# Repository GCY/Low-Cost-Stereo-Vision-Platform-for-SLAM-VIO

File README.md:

# Low-Cost-Stereo-Vision-Platform-for-SLAM-VIO

 - Step 1. Capture the [chessboard pattern](https://raw.githubusercontent.com/opencv/opencv/master/doc/pattern.png) picture from Left and Right Camera.
 - Step 2. Run "Stereo Camera Calibration"
 - Step 3. Calibration stereo camera phase, execute initUndistortRectifyMap with "extrinsics.yml" and "intrinsics.yml" befor cv::remap
 - Step 4. Create StereoBM or SGBM object to calculate depth map.
 - Step 5. Cet point cloud from depth map and baseline.

## Mac OS X

### Dependence
 - wxWidgets 3.0.4
 - OpenCV 4.4.0
 - libcurl 7.54.0
 
### Build

```cpp

cd ./App/Mac/wxStereoCamera
make

```

## Win10

### Dependence
 - wxWidgets 3.1.4
 - OpenCV 4.4.0
 - libcurl 7.67.0
 
 ### Build
 ```cpp
 Build App/Win10/wxStereoCamera/wxStereoCamera.sln with Visual Studio Community 2019
 ```

## Reference
 - [ESP32 CAM MJPEG Stream Decoder and Control Library](https://github.com/GCY/ESP32-CAM-MJPEG-Stream-Decoder-and-Control-Library)

Licensing
=======
Copyright (C) 2020  TonyGUO <https://github.com/GCY>.

This program is free software: you can redistribute it and/or modify
it under the terms of the GNU General Public License as published by
the Free Software Foundation, either version 3 of the License, or
(at your option) any later version.

This program is distributed in the hope that it will be useful,
but WITHOUT ANY WARRANTY; without even the implied warranty of
MERCHANTABILITY or FITNESS FOR A PARTICULAR PURPOSE.  See the
GNU General Public License for more details.

You should have received a copy of the GNU General Public License
along with this program.  If not, see <http://www.gnu.org/licenses/>.

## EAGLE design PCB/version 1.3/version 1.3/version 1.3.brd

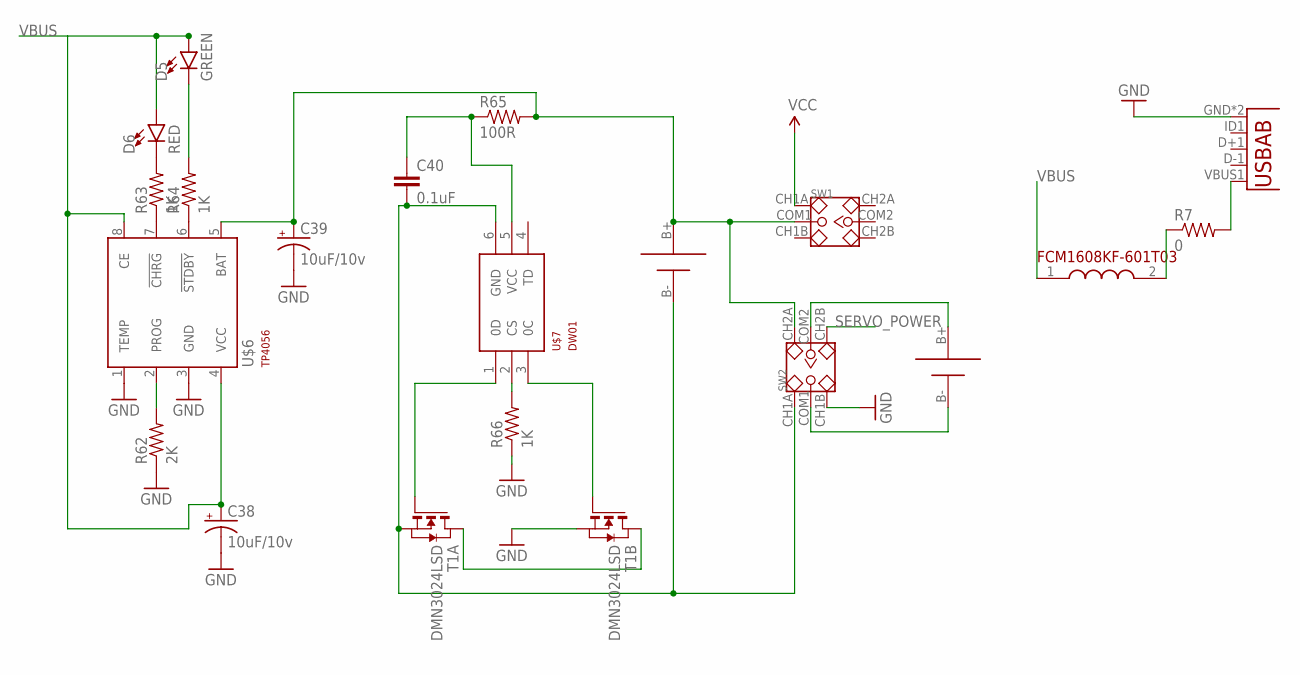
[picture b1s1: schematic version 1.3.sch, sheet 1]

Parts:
C38, C39: 10uF/10v; EIA3216-KIT
C40: 0.1uF; 0603-CAP
D5: GREEN; LED-0603
D6: RED; LED-0603
R7: 0; 0805
R62: 2K; 0603-RES
R63, R64, R66: 1K; 0603-RES
R65: 100R; 0603-RES
SW1, SW2: SMD-TOGGLE-SWITCH-2CH(2X3P-7X3.5MM); SW6-2.54-SMD-7.0X3.5X1.5MM
T1: DMN3024LSD; TSSOP-8
U1: USB""; USB-MICRO-SMD
U$4: FCM1608KF-601T03
U$5, U$8: 18650SMD
U$6: TP4056; SOT23-8
U$7: DW01; SOT23-6

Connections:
GND: C38.C (-), C39.C (-), R62.1, R66.1, SW2.CH1B, T1.6 (S), T1.7 (S), U1.GND, U1.GND1 (GND), U$6.1 (TEMP), U$6.3 (GND); also elsewhere on the board
unnamed: R7.2, U1.VBUS1 (VBUS)
unnamed: C39.A (+), R65.2, SW1.COM1, SW2.CH2A, U$5.B+, U$6.5 (BAT)
unnamed: SW2.COM2, U$8.B+
unnamed: SW2.COM1, U$8.B-
unnamed: R7.1, U$4.2 (2.OUT)
unnamed: R62.2, U$6.2 (PROG)
unnamed: R63.1, U$6.7 (!CHRG)
unnamed: R64.1, U$6.6 (!STDBY)
unnamed: D6.C, R63.2
unnamed: D5.C, R64.2
unnamed: C40.1, R65.1, U$7.5 (VCC)
unnamed: C40.2, SW2.CH1A, T1.2 (S), T1.3 (S), U$5.B-, U$7.6 (GND)
unnamed: T1.4 (G), U$7.1 (0D)
unnamed: R66.2, U$7.2 (CS)
unnamed: T1.1 (D), T1.8 (D)
unnamed: T1.5 (G), U$7.3 (0C)
SERVO_POWER: SW2.CH2B; also elsewhere on the board
VBUS: C38.A (+), D5.A, D6.A, U$4.1 (1.IN), U$6.4 (VCC), U$6.8 (CE)
VCC: SW1.CH1A; also elsewhere on the board

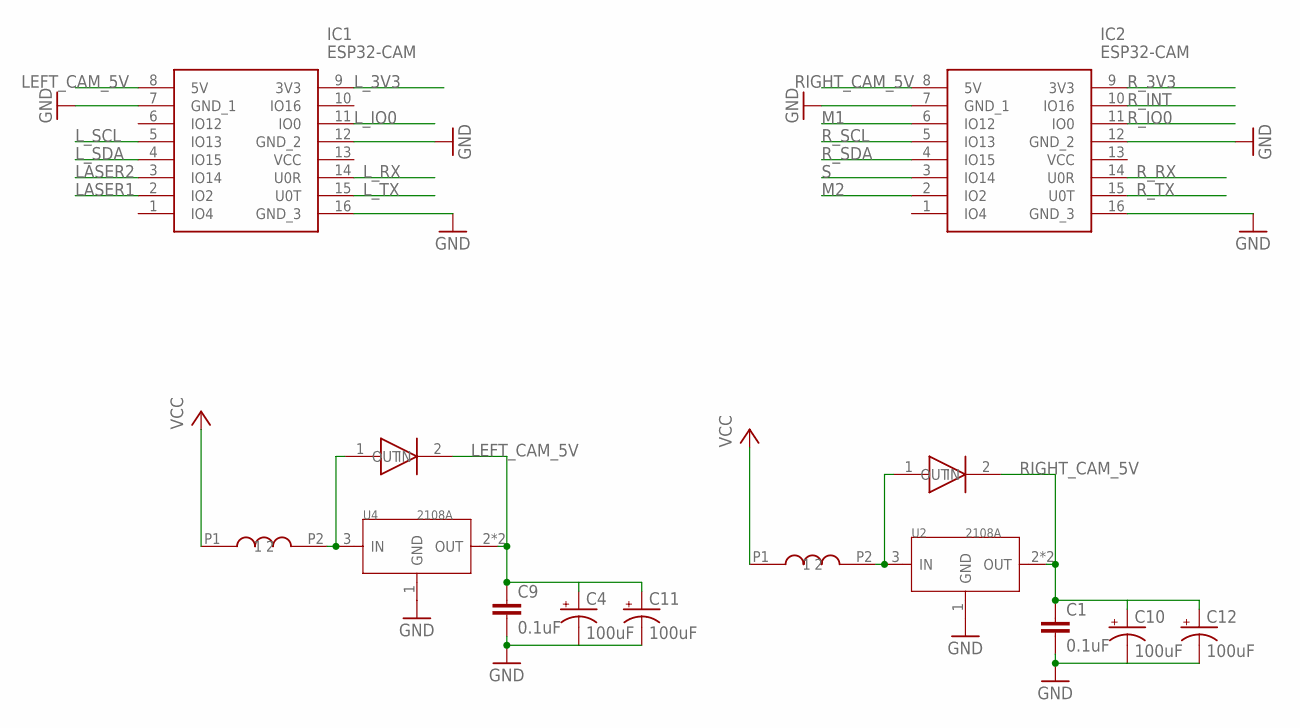
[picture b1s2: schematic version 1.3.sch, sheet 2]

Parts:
C1, C9: 0.1uF; 0603-CAP
C4, C10, C11, C12: 100uF; E/7260-38R
IC1, IC2: ESP32-CAM; ESP32CAM
U2, U4: 2108A; SOT-89
U$13, U$16: CD54
U$14, U$15: SMA-SS34

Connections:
GND: C1.2, C4.-, C9.2, C10.-, C11.-, C12.-, IC1.7 (GND_1), IC1.12 (GND_2), IC1.16 (GND_3), IC2.7 (GND_1), IC2.12 (GND_2), IC2.16 (GND_3), U2.1 (GND), U4.1 (GND); also elsewhere on the board
LASER1: IC1.2 (IO2); also elsewhere on the board
LASER2: IC1.3 (IO14); also elsewhere on the board
LEFT_CAM_5V: C4.+, C9.1, C11.+, IC1.8 (5V), U4.2 (OUT), U4.4 (OUT), U$14.2 (OUT); also elsewhere on the board
L_3V3: IC1.9 (3V3); also elsewhere on the board
L_IO0: IC1.11 (IO0); also elsewhere on the board
L_RX: IC1.14 (U0R); also elsewhere on the board
L_SCL: IC1.5 (IO13); also elsewhere on the board
L_SDA: IC1.4 (IO15); also elsewhere on the board
L_TX: IC1.15 (U0T); also elsewhere on the board
M1: IC2.6 (IO12); also elsewhere on the board
M2: IC2.2 (IO2); also elsewhere on the board
unnamed: U4.3 (IN), U$13.P2 (2), U$14.1 (IN)
unnamed: U2.3 (IN), U$15.1 (IN), U$16.P2 (2)
RIGHT_CAM_5V: C1.1, C10.+, C12.+, IC2.8 (5V), U2.2 (OUT), U2.4 (OUT), U$15.2 (OUT); also elsewhere on the board
R_3V3: IC2.9 (3V3); also elsewhere on the board
R_INT: IC2.10 (IO16); also elsewhere on the board
R_IO0: IC2.11 (IO0); also elsewhere on the board
R_RX: IC2.14 (U0R); also elsewhere on the board
R_SCL: IC2.5 (IO13); also elsewhere on the board
R_SDA: IC2.4 (IO15); also elsewhere on the board
R_TX: IC2.15 (U0T); also elsewhere on the board
S: IC2.3 (IO14); also elsewhere on the board
VCC: U$13.P1 (1), U$16.P1 (1); also elsewhere on the board

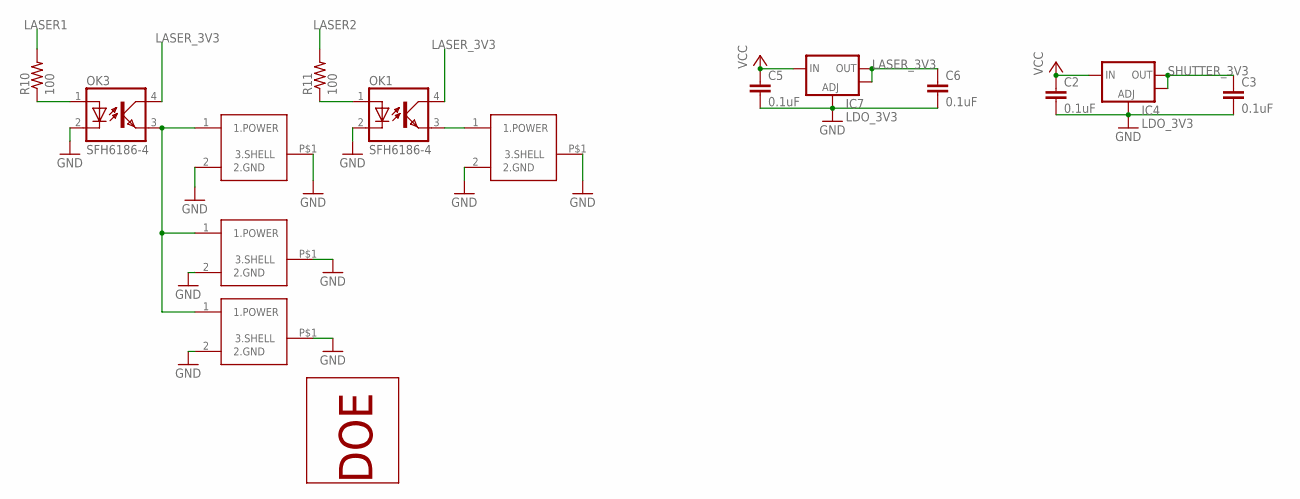
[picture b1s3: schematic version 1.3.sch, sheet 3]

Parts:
C2, C3, C5, C6: 0.1uF; 0603-CAP
IC4, IC7: LDO_3V3; SOT223
OK1, OK3: SFH6186-4; SMD4-7
R10, R11: 100; 0603-RES
U$1, U$2, U$9: OD-6.5MM-LASER
U$3: DOE-MODULE
U$20: OD-12MM-LASER

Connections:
GND: C2.2, C3.2, C5.2, C6.2, IC4.1 (ADJ), IC7.1 (ADJ), OK1.2 (C), OK3.2 (C), U$1.2 (2.GND), U$1.P$1 (3.SHELL), U$2.2 (2.GND), U$2.P$1 (3.SHELL), U$9.2 (2.GND), U$9.P$1 (3.SHELL), U$20.2 (2.GND), U$20.P$1 (3.SHELL); also elsewhere on the board
LASER1: R10.2; also elsewhere on the board
LASER2: R11.2; also elsewhere on the board
LASER_3V3: C6.1, IC7.2 (OUT), IC7.4 (OUT), OK1.4 (COL), OK3.4 (COL)
unnamed: OK3.3 (EMIT), U$1.1 (1.POWER), U$2.1 (1.POWER), U$9.1 (1.POWER)
unnamed: OK1.3 (EMIT), U$20.1 (1.POWER)
unnamed: OK3.1 (A), R10.1
unnamed: OK1.1 (A), R11.1
SHUTTER_3V3: C3.1, IC4.2 (OUT), IC4.4 (OUT); also elsewhere on the board
VCC: C2.1, C5.1, IC4.3 (IN), IC7.3 (IN); also elsewhere on the board

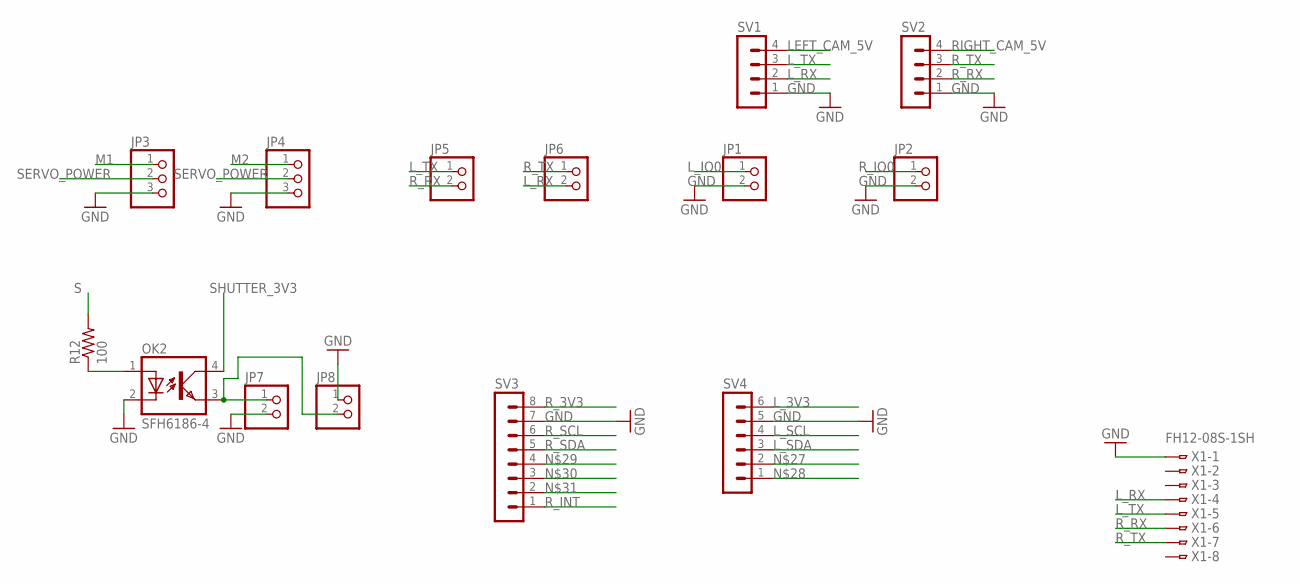
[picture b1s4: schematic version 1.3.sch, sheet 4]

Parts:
JP1, JP2, JP5, JP6, JP7, JP8: PINHD-1X2; 1X02
JP3, JP4: PINHD-1X3; 1X03
OK2: SFH6186-4; SMD4-7
R12: 100; 0603-RES
SV1, SV2: MA04-1
SV3: MA08-1
SV4: MA06-1
X1: FH12-08S-1SH

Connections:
GND: JP1.2, JP2.2, JP3.3, JP4.3, JP7.2, JP8.1, OK2.2 (C), SV1.1, SV2.1, SV3.7, SV4.5, X1.1; also elsewhere on the board
LEFT_CAM_5V: SV1.4; also elsewhere on the board
L_3V3: SV4.6; also elsewhere on the board
L_IO0: JP1.1; also elsewhere on the board
L_RX: JP6.2, SV1.2, X1.4; also elsewhere on the board
L_SCL: SV4.4; also elsewhere on the board
L_SDA: SV4.3; also elsewhere on the board
L_TX: JP5.1, SV1.3, X1.5; also elsewhere on the board
M1: JP3.1; also elsewhere on the board
M2: JP4.1; also elsewhere on the board
unnamed: OK2.1 (A), R12.1
unnamed: JP7.1, JP8.2, OK2.3 (EMIT)
RIGHT_CAM_5V: SV2.4; also elsewhere on the board
R_3V3: SV3.8; also elsewhere on the board
R_INT: SV3.1; also elsewhere on the board
R_IO0: JP2.1; also elsewhere on the board
R_RX: JP5.2, SV2.2, X1.6; also elsewhere on the board
R_SCL: SV3.6; also elsewhere on the board
R_SDA: SV3.5; also elsewhere on the board
R_TX: JP6.1, SV2.3, X1.7; also elsewhere on the board
S: R12.2; also elsewhere on the board
SERVO_POWER: JP3.2, JP4.2; also elsewhere on the board
SHUTTER_3V3: OK2.4 (COL); also elsewhere on the board

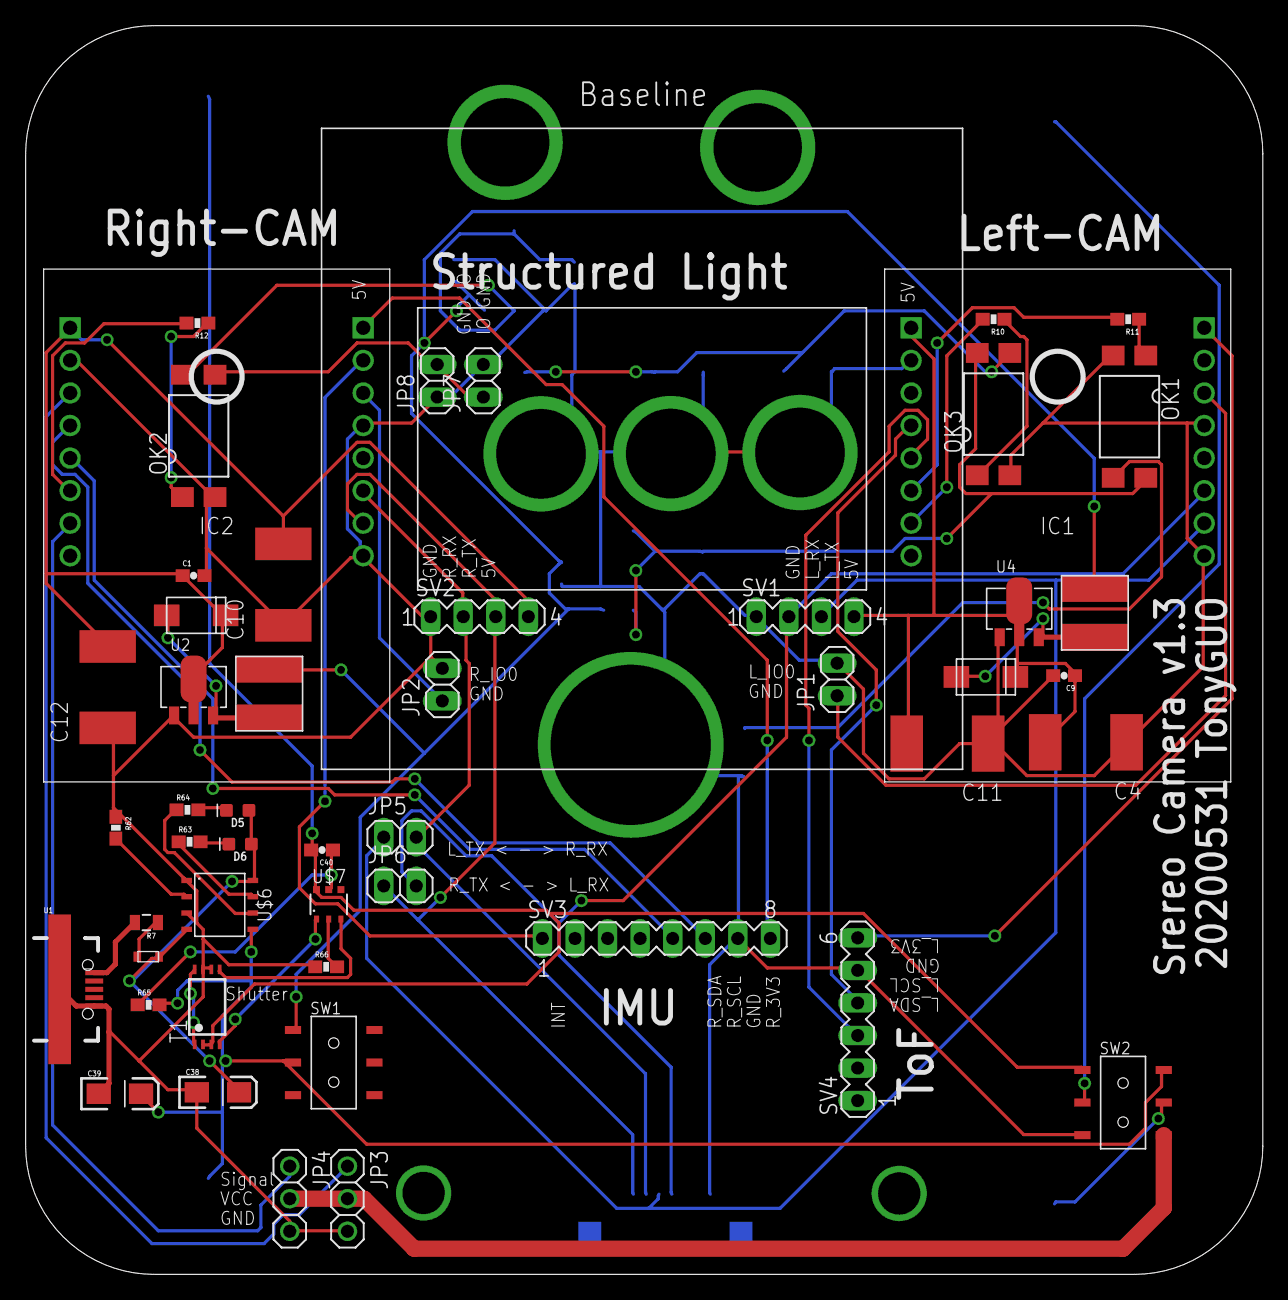
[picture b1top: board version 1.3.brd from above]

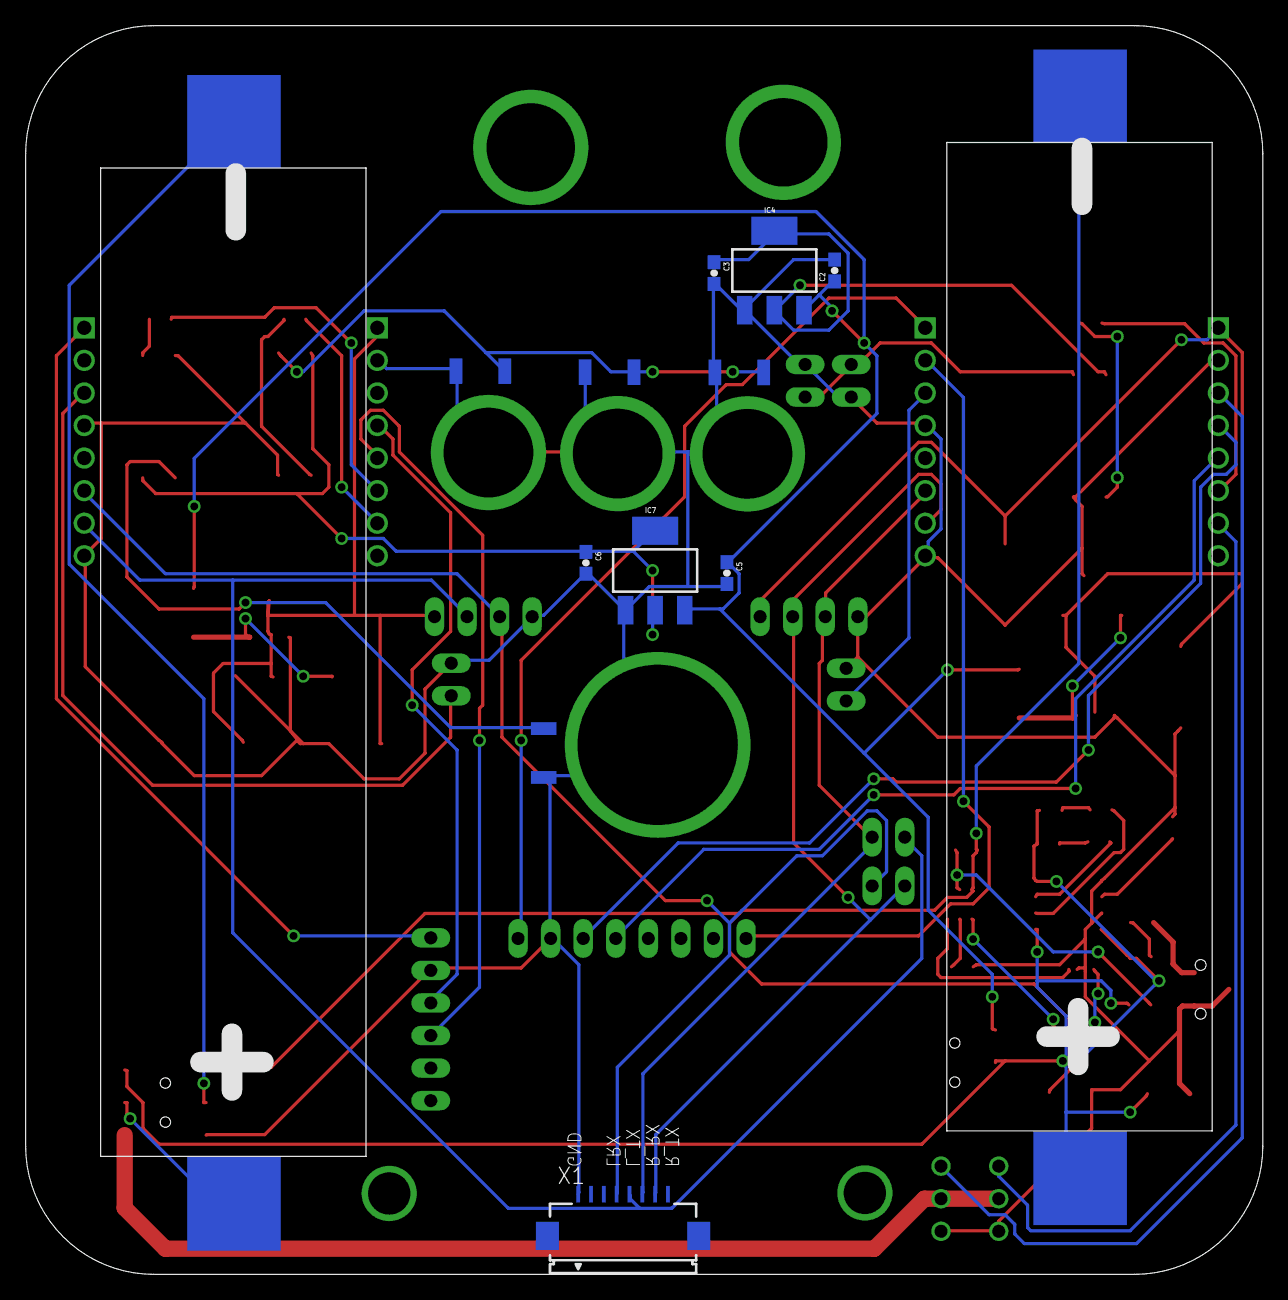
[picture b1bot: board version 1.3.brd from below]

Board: 2 copper layers, 96.5 x 97.4 mm, 64 parts (13 on the bottom side), 50 nets.

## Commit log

2020-05-28 imv1 demo
2020-05-28 stereo calibration tool
2020-05-28 v1 firmware
2020-05-28 v1.1 pcb horizontal
2020-05-30 wxStereoCamera v1.0
2020-05-31 vertical view
2020-06-13 v1.3 vertical
2020-06-13 v1.3
2020-06-13 laser control
2020-06-21 demo gif
2020-06-26 edit
2020-12-16 Mac PC-Host
2020-12-16 remove
2020-12-16 move
2020-12-17 delete
2020-12-17 mac and win10 app

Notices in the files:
parts and their libraries:
SparkFun-Capacitors: Licensing: CC v3.0 Share-Alike You are welcome to use this library for commercial purposes.
